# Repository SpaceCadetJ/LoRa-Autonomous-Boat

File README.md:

# LoRa Autonomous Boat Controller

An embedded-systems project spanning **STM32 firmware, LoRa communication, PCB reconstruction and a documented V2 redesign**. The original university boat controller is preserved as V1; the next vehicle node and a voice/text/location handheld are under development.

**Current milestone: engineering review edition.** The schematics, source code, parts and build procedures are available for inspection. V2 is not fabrication-ready, and the preserved V1 firmware build is not hardware-qualified.

[Portfolio case study](docs/portfolio/README.md) · [Application handbook](docs/applications/README.md) · [Build and assembly guide](docs/build/README.md) · [Latest verification](reviews/codex/design_completion/HANDOFF.md) · [Project history](REPORT.md)

| Existing controller | Developing controller |
| --- | --- |
|  |  |
| V1: 44 physical components, reconstructed from original fabrication evidence | V2: 118 physical references, 80 × 46 mm board draft |

These are CAD renders. They do not establish that the V2 board has been manufactured or tested.

## Explore the project

Clone or download the repository, then open [pm/index.html](pm/index.html) locally. For the complete interactive workspace with searchable BOMs, datasheets, drawings, connector evidence and assembly/programming guides:

```sh
node pm/tools/serve.mjs
```

Open **http://127.0.0.1:8765/pm/**. The viewer runs locally and requires no account or package installation. GitHub displays the HTML source; it does not run the viewer from a repository file link. See [viewer instructions](pm/README.md).

The [portfolio handoff](docs/portfolio/README.md) and [structured project data](docs/portfolio/portfolio.json) provide captions, asset paths, result evidence and claim boundaries for a portfolio site.

## Architecture and implementation

```mermaid
flowchart LR
  Handset[External handset] <-->|LoRa radio link| Radio[Reyax UART radio]
  Radio <-->|UART| MCU[STM32F446 vehicle controller]
  GPS[GNSS receiver] -->|NMEA UART| MCU
  MCU -->|PWM| ESC[Propulsion ESC]
  MCU -->|PWM| Servo[Steering servo]
  Battery[Battery and regulation] --> MCU
```

V1 firmware is bare-metal C using STM32 HAL/CMSIS, with UART radio commands, GPS parsing and two PWM outputs. The original handset source is not included. The current code has known failsafe, parsing and pin-role issues documented in the [firmware audit](docs/research/FIRMWARE_REVIEW_NOTES.md).

Hardware originated in Cadence OrCAD/Allegro and has been reconstructed in KiCad 9. Python tools generate and inspect schematics, compare complete pin groups and prepare assembly evidence. The viewer uses HTML, CSS and JavaScript with embedded project data; Node.js builds and validates it. GitHub Actions separates portable repository checks from optional native CAD and firmware jobs.

V2 adds draft provisions for protected power, a separate actuator rail, sensing and USB/debug access. The separate [Stage A diagnostic](firmware_v2/README.md) now builds for board identity and inactive actuator outputs. Corrected control firmware, autonomous navigation and the proposed voice/text/location handheld remain development targets. Voice airtime and RC coexistence must be validated before choosing handheld hardware.

## What has been demonstrated

| Deliverable | Recorded result | Evidence |
| --- | --- | --- |
| Readable schematic set | 15 annotated pages, visually inspected | [V1 PDF](docs/img/v1_schematic.pdf), [V2 PDF](docs/img/v2_schematic.pdf), [visual review](reviews/codex/professionalization/VISUAL_REVIEW.md) |
| Electrical preservation | All 172 V1 and 361 V2 pins preserved through the presentation changes | [Independent quality evidence](reviews/codex/professionalization/QUALITY_HANDOFF.md) |
| V1 firmware reconstruction | Two same-host builds produced identical ELF/HEX/BIN hashes; 36,528-byte BIN | [Build record](docs/build/FIRMWARE_HANDOFF.md) |
| Ordering and assembly | BOM reconciliation, held-part decisions, one-board/five-board candidate lists and assembly maps | [Ordering guide](docs/build/ORDERING.md) |
| Navigation and documentation | Searchable parts, selected datasheets, V1 connector atlas, source evidence and version-specific programming guides | [Workspace](pm/README.md), [build guide](docs/build/README.md) |
| Reproducible review | Regression tests, source hashes, native reports and preserved before/after evidence | [Review workflow](docs/build/REVIEW_WORKFLOW.md) |

The integrated V2 ground repair reduces **three unconnected PCB items to zero**, with zero ordinary DRC errors and unchanged warning/parity counts. The [fresh native review](reviews/codex/design_completion/native-review/REVIEW.md) preserves all 533 electrical pins. One V2 ERC warning remains; the strict review also flags the intentional PCB change against its older preservation baseline. Six [component-limit blockers](reviews/codex/design_completion/electrical/README.md) require circuit corrections before fabrication. No range, voice or autonomous-navigation performance is claimed by these software/CAD results.

## Build, review and contribute

- [V1 assembly and inspection](docs/build/ASSEMBLY_V1.md) · [V1 backup/flashing procedure](docs/build/FLASHING_V1.md)
- [V2 assembly review](docs/build/ASSEMBLY_V2.md) · [V2 firmware bring-up plan](docs/build/FLASHING_V2.md)
- [Safe schematic-only regeneration](docs/build/SCHEMATICS.md) · [Reproducible firmware build](docs/build/FIRMWARE_BUILD.md)
- [Independent review workflow](docs/build/REVIEW_WORKFLOW.md) · [Publication and portability record](reviews/codex/publication/README.md)

Do not run full PCB generation or routing merely to refresh drawings. The schematic-only command preserves the existing PCB, project and BOM. Native KiCad checks require KiCad 9; the V1 build requires the recorded GNU Arm toolchain. No CI job flashes real hardware.

The [IMU interface candidate](reviews/codex/imu_interface/README.md) now implements the proposed 1.8 V supply and I2C/interrupt translation in a separately checked schematic. It is available in the V2 viewer; live PCB integration is the next layout task.

## Next milestones

1. Correct the IMU's 1.8 V interface and the five remaining power/signal-limit findings; reconcile schematic-to-PCB differences.
2. Build on the separate Stage A diagnostic: freeze the operational protocol, implement supervised outputs and measure failsafe behavior.
3. Complete part/footprint qualification, the V2 connector atlas and staged physical bring-up.
4. Validate voice quality, radio airtime and RC scheduling before developing the handheld.

## Provenance and attribution

The original controller was a University of Arkansas EECS senior-design team project; the repository identifies May 2025 fabrication evidence. The current reconstruction, documentation and review tooling include AI-agent-assisted development. Individual original team contributions should be confirmed before using first-person portfolio claims.

`Allegro/` preserves original source evidence. Read [provenance and conversion limits](docs/A0_PROVENANCE.md) before interpreting the reconstructed geometry or inferred drill data. Third-party firmware and tools retain their existing notices; no new project-wide license is granted by this documentation.

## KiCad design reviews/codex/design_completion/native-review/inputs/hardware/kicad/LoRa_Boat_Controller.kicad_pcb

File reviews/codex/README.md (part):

# Start here: Codex review checkpoint

## Current actuator packet - ACT-04, 2026-10-12

The [isolated arm latch and annotated native sheets](actuator_latch/README.md) separate PC4 from OE while retaining R40 at OE. Native ERC is zero errors / the original AD0 warning; 396 existing memberships are preserved and exactly two change. The qualification and ACK sources remain unimplemented and default low. ACK while armed disables, a documented difference from ACT-03. Next: qualification/reset-release circuitry with fault retention and conditioned ACK; receiver readiness and watchdog sources remain held. This supersedes older next-task text below.

## Current actuator packet - ACT-03, 2026-10-12

The [interlock behavior and observability prototype](actuator_interlock/README.md) adds interactive fault scenarios, an executable deliberate-rearm contract and a receiver acceptance worksheet. Exact ACT-02 pin evidence confirms no receiver sensing and unused converter PG pins. No CAD/firmware change or new native acceptance is claimed. Next: isolated fault-dominant latch/OE gate with the PC4 request separated from OE and R40 retained; unimplemented qualifications must remain default-disabled. This supersedes older next-task text below.

## Current actuator packet - ACT-02, 2026-10-12

The [default-disabled translator and sequencing contract](actuator_enable/README.md) now has an annotated native schematic: TXU0102DCUR, PC4 arm signal and 10k hardware pulldown. Independent checks preserve 383 outside-boundary pins, both converters and ACT-01 source populations; 41 tests pass and ERC adds no findings. Firmware, ordering and live PCB are unchanged. Next: receiver-power observation and a hardware arm interlock, including independent ESC readiness in both populations. This supersedes older next-task text below.

## Current actuator packet - ACT-01, 2026-10-12

The [buffer supply and population review](actuator_supply/README.md) moves exactly four buffer/bypass pins to the dedicated 5 V converter, preserves both converter sheets and adds exact SMC diode identities with mutually exclusive BEC_ONLY/ONBOARD proposals. All 380 outside-boundary pins are preserved; no new ERC findings. A new C11 identity hold changes V2 ordering to 68 candidate / 39 held / 11 feature references, 35 candidate lines. Next: default-disabled buffer enable and power sequencing, followed by reservoir/transient and remaining integration gates. This supersedes older next-task text below.

## Current converter packet — BUCK5-A1, 2026-10-12

The [5 V converter and shared-feed review](buck_5v/README.md) now includes an annotated native LM76003 sheet: 119 components, 398 physical pins, all 339 outside-boundary pins preserved, zero ERC errors and the original warning. The first 3.3 V sheet is byte-identical. New SS34 SMC/SMA package findings are added to existing ordering holds; the 7 V full-load feed remains unqualified. Next: isolate the buffer supply from VSERVO and resolve exact OR-ing parts and supply population variants, then input-feed/leakage/damping and remaining integration gates. This entry supersedes older next-task text below.

## Current converter packet — BUCK33-A1, 2026-10-12

The [complete first 3.3 V converter](buck_3v3/README.md) now has a separate annotated sheet, exact supporting parts and native validation: 113 components, 361 pins, all 330 outside-boundary pins preserved, zero errors and the original ERC warning. This is an isolated INPUT-A1-derived candidate; live CAD, copper, purchasing and firmware remain unchanged. Capacitance, thermal, loop, input leakage and ADC gates remain open. Next: the isolated 5 V converter and its simultaneous-load budget, retaining 6S and the optional on-board actuator configuration. This entry supersedes older next-task text below.

## Current input-network packet — 2026-10-12

The [nonpolar reservoir and local bypass specification](input_capacitors/README.md) now includes exact screened identities, an annotated connection drawing, capacitance requirements and a native-checked TDK land-pattern proposal. No circuit changed; source damping, effective capacitance and complete leakage remain integration gates. Next: the isolated first 3.3 V wider-voltage converter cell with explicit pin delta and those holds retained. This entry supersedes older next-task text below.

## Latest circuit revision: IMU2

Start with [IMU2 and the next task](imu_bias_filter/README.md). The recommended 100 pF bias filter is verified in an isolated schematic; prior IMU1 and placement evidence remain immutable. Next: the 6S protection/power-package envelope, then complete-circuit routing.

## Latest bounded packet: placement feasibility

[Placement study and next task](imu_placement/README.md) preserves all original copper and placements. It verifies courtyard fit but rejects integration on untouched copper, with 136 native errors. Next: disposition the recommended bias filter and establish the 6S power-package envelope before final routing.

## Latest bounded packet: IMU interface candidate

[IMU candidate and next task](imu_interface/README.md) implements and independently checks the 1.8 V supply/bus/interrupt circuit in an isolated schematic. Live CAD and purchasing exports remain unchanged. Assess placement on a corrected PCB copy before integration.

## Current application and electrical completion packet

Start with [design_completion/HANDOFF.md](design_completion/HANDOFF.md), [application guides](../../docs/applications/README.md) and the [V2 diagnostic](../../firmware_v2/README.md). The current work connects application procedures to actual board/firmware readiness, repairs the three ground connections, identifies six component-limit blockers, and adds a pin-checked Stage A image. The previously published integration is on `main` and `v2-design`; earlier primary-ownership and no-push statements below are historical. Operational control firmware, electrical corrections and bench qualification remain separate open work.

## Earlier checkpoint — 2026-09-17, schematic and build review edition

Read [professionalization/HANDOFF.md](professionalization/HANDOFF.md) and [docs/build/README.md](../../docs/build/README.md) first. Jay authorized Codex to continue the professional schematics, purchasing/assembly, V1/V2 programming and review workflow while the other agent is inactive. Current ownership supersedes the earlier reservations below.

The delivered packet includes fifteen annotated schematic pages, verified preservation of 172 V1 / 361 V2 pins, a protected schematic-only generator command, ordering candidates/holds and assembly maps, a reproducible unqualified V1 firmware build, separate flashing guides and a manual CI definition. Strict combined review remains failed for one pre-existing V2 ERC warning. V2 also has three unconnected PCB entries, warnings/parity discrepancies and no firmware image; it is not fabrication-ready. The viewer now presents these current results beside the historic S2 evidence.

The next smallest packet is a pad-level disposition of the three V2 open connections and U6 AD0 warning, followed by a reviewed V2 pin/protocol contract. Avoid full CAD regeneration/rerouting during documentation work. All source/output hashes, reproduction commands and remaining limits are in the linked handoff. The hourly continuation prompt has been updated to this scope and remains quiet for non-actionable results.

## Previous checkpoint — 2026-09-17, viewer delivery

This section supersedes the initial intake state below. Resume through [pm/README.md](../../pm/README.md), then the latest root [handoff](../../HANDOFF.md) and [ownership](../../FILE_OWNERSHIP.md). Check Git status/HEAD before writing; the primary remains responsible for CAD, firmware, generators and Git integration. Codex owns `pm/**`, `docs/atlas/**`, `reviews/**`; coordination files are append-only.

- The local [interactive viewer](../../pm/index.html) includes V1 and V2 design assets, searchable BOMs and selected manufacturer references, the V1 connector atlas, source/protocol proposals, independent versus reported checks, findings-to-requirements links, decisions, documents and exported review notes. It opens directly or through the loopback server described in its README.
- [V1 atlas](../../docs/atlas/README.md): 12 connectors/test points and 36 pins, traced from source evidence with firmware citations. Physical orientation and bench readings remain unverified. V2 atlas is not yet done.
- [S2 independent verification](S2_VERIFICATION.md): historic `639e08f` only. All 172 pins / 44 parts agree, ERC 0, DRC 0 errors / 0 unconnected / 67 warnings, hole centers 53/53. Additional native parity: 139 classified metadata warnings. No electrical mismatch found; no-change schematic update workflow and V5 drill sizes remain unverified. The earlier global blocked label was narrowed; raw results did not change.
- Primary V2 release at `a6316e9` / `v2-design-draft` reports 118 parts, 71 nets, 68 grouped BOM lines and two open ground connections. The current CSV independently parses as 67 component rows totaling 118 parts; the report count is stale. Treat V2 numbers as reported, pending independent verification. Current source documents contain 35 distinct V1 findings and 45 requirements.
- Standalone files in `firmware_prototype/` are uncompiled review proposals. No functional firmware fix was integrated.
- Jay requires **voice + text + location**. The primary handoff additionally reports expanded vehicle/fleet scope; wait for its architecture/requirements documents before asserting that expanded scope is implemented. Validate voice/RC coexistence before radio selection. `REQ-CTL-01` currently says a default **1.0 s** loss timeout; the primary prompt's **500 ms** summary conflicts and must be reconciled in the RF packet.

**Next smallest packet:** independently snapshot the released V2 inputs, record hashes and run ERC/DRC plus part/net/BOM inventory in `reviews/codex/` without invoking generators or changing source CAD. Then review one power/control subsystem against actual requirements. Later packets: V2 atlas, protocol prototype build/tests, quantitative voice/RC coexistence, handheld/application views from released documents.

An hourly continuation automation is active. It works bounded packets in released scopes and should notify only on meaningful deliverables, new blocking findings or required decisions. Account/runtime availability may interrupt runs; these files are the durable resume context.

## Historical initial intake — retained for context

Updated 2026-09-17 UTC. User objective: understand and improve the conversion, documentation and readability first; develop a general-purpose LoRa controller family later. Primary agent is still active. Codex has made no CAD, firmware, source-evidence or Git-history changes.

## Read in this order

1. This file and root [ownership](../../FILE_OWNERSHIP.md), [handoff](../../HANDOFF.md), [status](../../AGENT_STATUS.md).
2. [Assessment](ASSESSMENT.md): corrected baseline, findings, gate matrix and safe continuation.
3. [Platform concept](PLATFORM_CONCEPT.md): block/state diagrams, shared interfaces and documentation design.
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
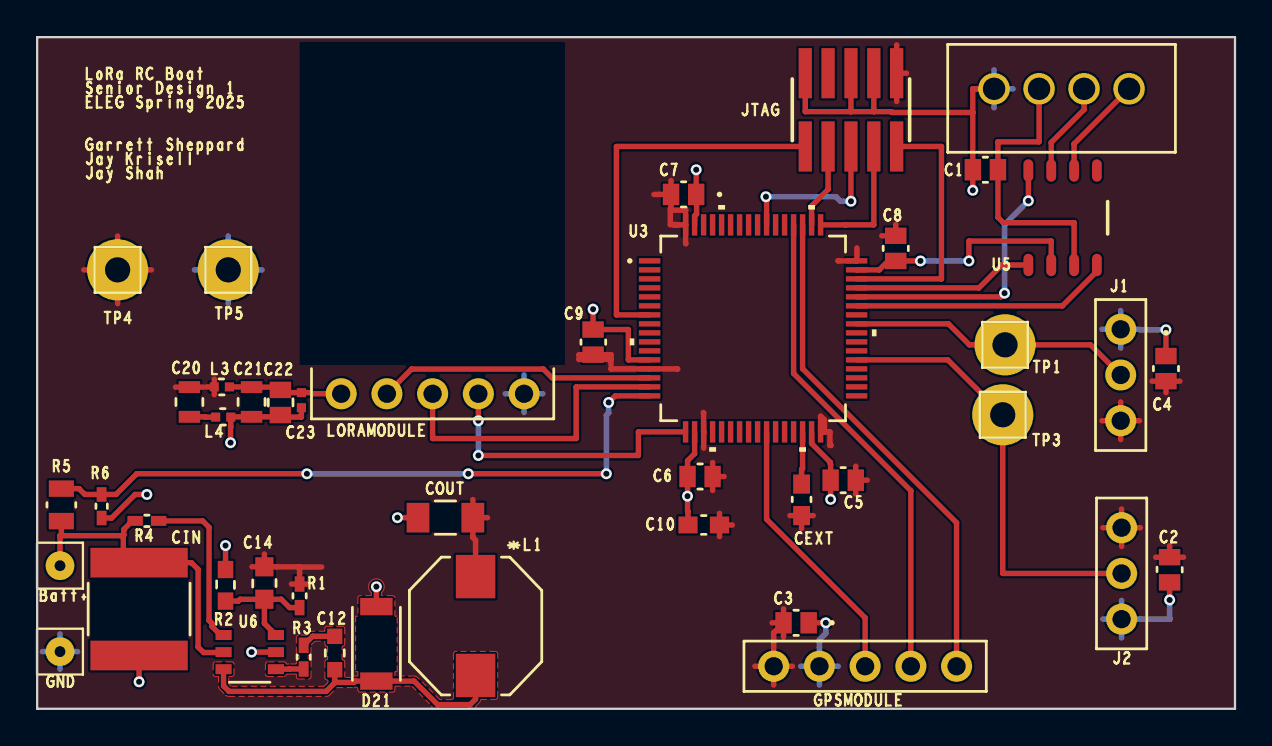
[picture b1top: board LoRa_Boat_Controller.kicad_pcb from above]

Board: 2 copper layers, 66.5 x 37.3 mm, 44 parts (0 on the bottom side), 31 nets.

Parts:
C1, C2, C3, C4, C5, C6, C7, C8, C9, C22: .1uF; CAP_KGM21_KAV-L
C10: 4.7uF; CAP_0603_CL10A_1P6XP8_SAM-M
C12: .1uf; CAP_CL10_SAM-M
C14: 470pF; CAP_0603G_AVX-M
C20, C21: 10uF; G-21_MUR-L
C23: 47pF; CAP_GJM1555C1H220JB01__MUR-L
CANHEADER1: CONN_B4B-XH-A; CONN_B4B-XH-A_JST
CEXT1: 4.7 uF; CAP_0603_CL10A_1P6XP8_SAM-M
CIN1: 10uF; CAP_NTS_55_2P8T_NIP
COUT1: 10uf; G-31_MUR-M
D21: DIODE_MFLAT; M-FLAT_TOS-L
GND1: Battery-; amv_con1
GPSMODULE1: CONN5_1LFBN-RC; CONN5_1LFBN-RC_SUL
JTAG1: FTSH-105-XX-X-DV; SAMTEC_FTSH-105-XX-X-DV
L1: 4.7uh; IND_7045_TDK
L3, L4: INDUCTOR; IND_BLM15_0402_MUR-L
LORAMODULE1: CONN5_1LFBN-RC; CONN5_1LFBN-RC_SUL
R1: 15K; RC0402N_PAN-M
R2: 4.7K; RC0603N_YAG-M
R3: 51; RC0402N_YAG-M
R4: 5.1K; RC0402N_PAN-M
R5: 30K; RES_R0805_ROM-M
R6: 10K; RES_1005_SAM-M
SPEEDCONTROLLER1: CONN_PPTC031; CONN_PPTC031_SUL
STEERINGSERVO1: CONN_PPTC031; CONN_PPTC031_SUL
TP1, TP3, TP4, TP5: TEST POINT; amv_test_point
U3: STM32F4XXR2; LQFP64-10x10mm
U5: TCAN1042H-Q1D; D0008A_L
U6: R1240N001x; SOT-23-6W_PE-SOT23-6W-0512_NMD
VIN1: Battery+; amv_con1

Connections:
+3V3: C2.2, C3.2, C4.2, C5.2, C6.2, C7.2, C8.2, C9.2, C10.2, C14.1, C20.2, CEXT1.2, COUT1.2, GPSMODULE1.1, JTAG1.1, L1.1, L3.2, R1.1, SPEEDCONTROLLER1.1, STEERINGSERVO1.1, TP4.1, U3.13 (VDDA/VREF+), U3.19 (VDD), U3.32 (VDD_2), U3.48 (VDD_3), U3.64 (VDD_4)
ADC_VBAT: R5.2, R6.2, U3.16 (PA2)
BST: R3.2, U6.4 (BST)
BST_RC: C12.2, R3.1
CANH: CANHEADER1.3, U5.7 (CANH)
CANL: CANHEADER1.4, U5.6 (CANL)
CAN_RXD_PA10: U3.43 (PA10), U5.4 (RXD)
CAN_STB_PA11: U3.44 (PA11), U5.8 (STB)
CAN_TXD_PA12: U3.45 (PA12), U5.1 (TXD)
CAN_VCC: C1.2, CANHEADER1.2, U5.3 (VCC)
EN: R4.2, U6.1 (CE)
FB_DIV: C14.2, R1.2, R2.1, U6.6 (VFB)
GND: C1.1, C2.1, C3.1, C4.1, C5.1, C6.1, C7.1, C8.1, C9.1, C10.1, C21.1, C22.1, C23.1, CANHEADER1.1, CIN1.1, COUT1.1, D21.1, GND1.1, GPSMODULE1.2, JTAG1.3, JTAG1.5, JTAG1.9, L4.1, LORAMODULE1.5, R2.2, R6.1, SPEEDCONTROLLER1.3, STEERINGSERVO1.3, TP5.1, U3.12 (VSSA/VREF-), U3.18 (VSS), U3.31 (VSS_2), U3.47 (VSS_3), U3.63 (VSS_4), U5.2 (GND), U6.5 (GND)
GPS_PB0: GPSMODULE1.3, U3.26 (PB0)
GPS_RX_PC11: GPSMODULE1.4, U3.52 (PC11)
GPS_TX_PC10: GPSMODULE1.5, U3.51 (PC10)
LORA_FILT: C20.1, L4.2
LORA_RST_PA3: LORAMODULE1.4, U3.17 (PA3)
LORA_RX_PA1: LORAMODULE1.3, U3.15 (PA1)
LORA_TX_PA0: LORAMODULE1.2, U3.14 (PA0)
LORA_VCC: C21.2, C22.2, C23.2, L3.1, LORAMODULE1.1
NRST: JTAG1.10, U3.7 (NRST)
PWM_PA8_ESCHDR: SPEEDCONTROLLER1.2, TP1.1, U3.41 (PA8)
PWM_PC6_SERVOHDR: STEERINGSERVO1.2, TP3.1, U3.37 (PC6)
SWCLK: JTAG1.4, U3.49 (PA14)
SWDIO: JTAG1.2, U3.46 (PA13)
SWO_TDO: JTAG1.6, U3.55 (PB3)
SW_NODE: C12.1, D21.2, L1.2, U6.3 (LX)
TDI: JTAG1.8, U3.50 (PA15)
VCAP1: CEXT1.1, U3.30 (VCAP_1)
VIN_RAW: CIN1.2, R4.1, R5.1, U6.2 (VIN), VIN1.1

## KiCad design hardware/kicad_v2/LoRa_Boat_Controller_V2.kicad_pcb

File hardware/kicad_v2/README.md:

# LoRa Boat Controller V2 — KiCad 9 project (Phase C draft)

Electrical intent is generated from `tools/v2_design.py`; schematic presentation is controlled by `../kicad/tools/schematic_layout.py` and the shared renderer. Keep source and generated outputs together. The [build guide](../../docs/build/README.md), [schematic editing procedure](../../docs/build/SCHEMATICS.md) and [current independent checks](../../reviews/codex/professionalization/QUALITY_HANDOFF.md) describe the latest review packet. Existing PCB routing is preserved by schematic-only commands.

| File | What it is |
|---|---|
| `LoRa_Boat_Controller_V2.kicad_pro` | project: netclasses (Default 0.25 mm / 0.15 mm, Power 0.6 mm / 0.2 mm), DRC severities, board rules (0.127 mm min clearance / track, 0.3 mm edge, 0.6 mm min via) |
| `LoRa_Boat_Controller_V2.kicad_sch` + `Power/MCU/Radio/Navigation/Actuators/Debug.kicad_sch` | root sheet with hierarchical pins + six sub-sheets (ERC: 0 errors, 1 accepted warning — U6 SDO/AD0 tied to GND) |
| `LoRa_Boat_Controller_V2.kicad_pcb` | 80 × 46 mm 2-layer board, 118 footprints, GND pours both sides, autorouted with freerouting (see `tools/route_v2.py`) |
| `LoRa_Boat_Controller_V2.kicad_sym` / `.pretty/` | project symbols (VSERVO) and footprints (QFN-24 3 × 3 mm 0.4 mm no-EP for the ICM-20948) |
| `fp-lib-table`, `sym-lib-table` | project libraries: `LoRa_Boat_Controller` (reused V1 footprints/symbols from `../kicad/`) and `LoRa_Boat_Controller_V2` |
| `_build/` | (git-ignored) DSN/SES, freerouting log, DRC/ERC reports, placement report, BOM JSON |

## Tool chain (run from the repo root)

```bash
python hardware/kicad_v2/tools/gen_v2.py check                                   # design-rule sanity: every pin either in a net or in NC_PINS
python hardware/kicad_v2/tools/gen_v2.py sch                                     # schematic-only refresh; preserves PCB/project/BOM
python hardware/kicad/tools/export_review.py                                    # PDF/SVG rendering only; no CAD generation
"C:/Users/Jay/AppData/Local/Programs/KiCad/9.0/bin/python.exe" hardware/kicad_v2/tools/placement_check.py   # courtyard overlaps / parts off the board
"C:/Users/Jay/AppData/Local/Programs/KiCad/9.0/bin/kicad-cli.exe" sch erc --severity-all -o hardware/kicad_v2/_build/erc.rpt hardware/kicad_v2/LoRa_Boat_Controller_V2.kicad_sch
"C:/Users/Jay/AppData/Local/Programs/KiCad/9.0/bin/python.exe" hardware/kicad_v2/tools/route_v2.py all     # DSN (B.Cu GND plane only) -> freerouting -> SES import -> pour fill
"C:/Users/Jay/AppData/Local/Programs/KiCad/9.0/bin/kicad-cli.exe" pcb drc --severity-error -o hardware/kicad_v2/_build/drc.rpt hardware/kicad_v2/LoRa_Boat_Controller_V2.kicad_pcb
```

`gen_v2.py pcb` explicitly replaces the PCB with an unrouted board; `gen_v2.py all` (also the legacy no-argument default) regenerates libraries, schematic, project, unrouted PCB and BOM. Use those only for an intentional full rebuild. `check`, `bom` and `sch` have separate scopes; `sch` no longer destroys routing. An isolated regression test verifies that separation.

`route_v2.py` needs Java 21 and `freerouting-2.1.0.jar` at `%LOCALAPPDATA%\freerouting\` (or `FREEROUTING_JAR`). Routing is separate from schematic presentation; do not reroute merely to refresh drawings. The routing command above remains an explicit board mutation, outside the presentation-only workflow.

## Design source (`tools/v2_design.py`)

- `PARTS`: ref -> (symbol, footprint, value, MPN, manufacturer, sheet, description). `NETS`: net -> pins as `REF-number` or `REF.pinname`. `NC_PINS`: pins deliberately left open (everything else must be in a net, `gen_v2.py check` fails otherwise).
- `POWER_NETS`: which nets are drawn with power symbols; `SHEETS`: sheet names/paper/descriptions; `PLACE`: ref -> (x, y, rotation) in board mm from the top-left corner; `MOUNT_HOLES`, `BOARD_W/H`, `KEEPOUTS`.
- `PRICE_USD` / `PRICE_DATE`: qty-1 catalogue prices used by `docs/BOM_V2.csv` (estimates; re-quote at order time).

Requirement traceability is in the schematic sheet descriptions and in `docs/V2_REQUIREMENTS.md` (REQ-xx ids); the design decisions still open for Jay are in `BLOCKERS.md`.

## Known state of this draft

Current independent results supersede the historical routing count below: **3 unconnected entries, 101 DRC warnings, 212 schematic-parity entries**, zero DRC errors; ERC has one pre-existing U6 AD0 pin-type warning. No fabrication acceptance. [Assembly maps and procedures](../../docs/build/ASSEMBLY_V2.md) are now available; physical orientation and device/footprint qualification remain open.

- DRC 0 violations, **2 unconnected GND connections**: two pour islands (near U1 at board (42, 18.5) mm and near U7 at (55.7, 9.2) mm) are fenced in by other-net tracks on both layers. `route_v2.py import` stitches what it can (one of three islands on this layout); the last two need a hand-placed via each in KiCad (or a rip-up of the fencing track). The next layout pre-places a GND via next to every fine-pitch GND pad before routing to avoid this.
- Autorouted, not hand-optimised: expect to tidy the buck-converter loops (U2/L1/D3/C5-C6 and U3/L2/D4/C8-C9), the crystal traces and the USB pair before fabrication; keep the placement.
- Silkscreen is reference designators only; no assembly drawing yet.
- Footprints for new parts come from the KiCad 9 standard library on this machine (`KICAD_FOOTPRINT_DIR`), embedded into the board at generation time.

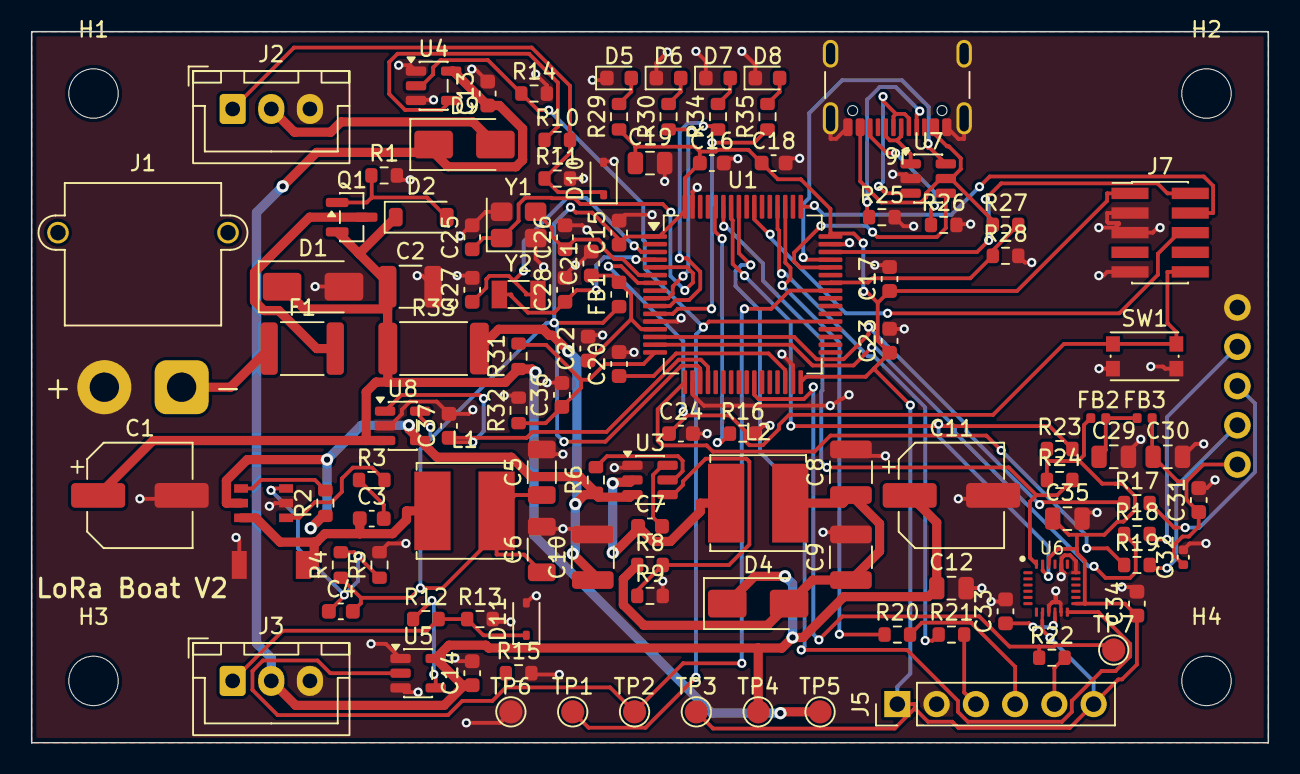
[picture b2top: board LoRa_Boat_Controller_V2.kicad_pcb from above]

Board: 2 copper layers, 80.0 x 46.0 mm, 118 parts (0 on the bottom side), 71 nets.

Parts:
C1: 47uF 50V; CP_Elec_6.3x7.7
C2, C10: 10uF 50V; C_1210_3225Metric
C3: 100nF 50V; C_0603_1608Metric
C4: 470pF; C_0603_1608Metric
C5, C6: 10uF 25V; C_1206_3216Metric
C7, C13, C14, C15, C16, C17, C18, C22, C23, C24, C31, C33, C34, C36, C37: 100nF; C_0603_1608Metric
C8, C9: 22uF 16V; C_1210_3225Metric
C11: 100uF 10V; CP_Elec_6.3x7.7
C12: 10uF 16V; C_0805_2012Metric
C19, C29, C30, C35: 10uF 10V; C_0805_2012Metric
C20: 4.7uF 10V; C_0603_1608Metric
C21: 1uF; C_0603_1608Metric
C25, C26: 15pF C0G; C_0603_1608Metric
C27, C28: 10pF C0G; C_0603_1608Metric
C32: 47pF; C_0402_1005Metric
D1: SMAJ33A; D_SMA
D2: 10V; D_SOD-123
D3: CMS06; M-FLAT_TOS-L
D4, D9: SS34; D_SMA
D5: PWR green; LED_0603_1608Metric
D6: LINK blue; LED_0603_1608Metric
D7: FIX yellow; LED_0603_1608Metric
D8: FAULT red; LED_0603_1608Metric
D10, D11: PESD5V0S1BA; D_SOD-323
F1: 3A; Fuse_1812_4532Metric
FB1: 600R; L_0603_1608Metric
FB2, FB3: 600R; L_0402_1005Metric
H1, H2, H3, H4: M3; MountingHole_3.2mm_M3
J1: BATTERY XT30; AMASS_XT30PW-M_1x02_P2.50mm_Horizontal
J2: ESC; JST_XH_B3B-XH-A_1x03_P2.50mm_Vertical
J3: SERVO; JST_XH_B3B-XH-A_1x03_P2.50mm_Vertical
J4: LoRa RYLR998; CONN5_1LFBN-RC_SUL
J5: GNSS; PinHeader_1x06_P2.54mm_Vertical
J6: USB-C; USB_C_Receptacle_GCT_USB4105-xx-A_16P_TopMnt_Horizontal
J7: SWD; PinHeader_2x05_P1.27mm_Vertical_SMD
L1, L2: 4.7uH 3A; L_Bourns_SRN6045TA
Q1: AO3401A; SOT-23
R1, R6, R8, R14, R15: 100k; R_0603_1608Metric
R2, R25, R26: 5.1k; R_0603_1608Metric
R3: 51R; R_0603_1608Metric
R4: 15k; R_0603_1608Metric
R5: 4.7k; R_0603_1608Metric
R9: 13.3k; R_0603_1608Metric
R10, R12, R17, R18, R19, R20, R21, R22: 100R; R_0603_1608Metric
R11, R13, R16: 10k; R_0603_1608Metric
R23, R24: 2.2k; R_0603_1608Metric
R27, R28, R31: 47k; R_0603_1608Metric
R29, R30, R34, R35: 1k; R_0603_1608Metric
R32: 6.8k; R_0603_1608Metric
R33: 0.02R 1W; R_2512_6332Metric
SW1: RESET; SW_Push_1P1T_NO_CK_KMR2
TP1: ESC_PWM; TestPoint_Pad_D1.5mm
TP2: SERVO_PWM; TestPoint_Pad_D1.5mm
TP3: +3V3; TestPoint_Pad_D1.5mm
TP4: VSERVO; TestPoint_Pad_D1.5mm
TP5: VIN_RAW; TestPoint_Pad_D1.5mm
TP6: GND; TestPoint_Pad_D1.5mm
TP7: PPS; TestPoint_Pad_D1.5mm
U1: STM32F446RET6; LQFP-64_10x10mm_P0.5mm
U2: R1240N001B-TR-FE; SOT-23-6W_PE-SOT23-6W-0512_NMD
U3: TPS54202; TSOT-23-6
U4, U5: 74AHCT1G125; SOT-23-5
U6: ICM-20948; QFN-24_3x3mm_P0.4mm_NoEP
U7: USBLC6-2SC6; SOT-23-6
U8: INA180A1; SOT-23-5
Y1: 8MHz; Crystal_SMD_3225-4Pin_3.2x2.5mm
Y2: 32.768kHz; Crystal_SMD_3215-2Pin_3.2x1.5mm

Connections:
+3V3: C4.2, C5.1, C6.1, C15.1, C16.1, C17.1, C18.1, C19.1, C23.1, C34.1, C35.1, FB1.1, FB2.1, J5.1, J5.6, J7.1, L1.2, R4.1, R23.1, R24.1, R29.1, TP3.1, U1.1, U1.19, U1.32, U1.48, U1.64, U6.8, U6.13, U6.22, U8.5
+5V_BUCK: C8.1, C9.1, D4.2, L2.2, R8.1
BEC_IN: D9.2, J2.2
BOOT0: R16.1, U1.60
BOOT_5V: C7.2, U3.6
BST_3V3: R3.2, U2.4
BST_RC: C3.2, R3.1
EN_3V3: R2.2, U2.1
EN_5V: R6.2, U3.5
ESC_SIG: D10.1, J2.1, R10.2, R11.1
ESC_SIG_5V: R10.1, U4.4
FB_3V3: C4.1, R4.2, R5.1, U2.6
FB_5V: R8.2, R9.1, U3.4
GND: C1.2, C2.2, C5.2, C6.2, C8.2, C9.2, C10.2, C11.2, C12.2, C13.2, C14.2, C15.2, C16.2, C17.2, C18.2, C19.2, C20.2, C21.2, C22.2, C23.2, C24.2, C25.2, C26.2, C27.2, C28.2, C29.2, C30.2, C31.2, C32.2, C33.2, C34.2, C35.2, C36.2, C37.2, D1.2, D3.1, D5.1, D6.1, D7.1, D8.1, D10.2, D11.2, J1.2, J2.3, J3.3, J4.5, J5.2, J6.A1, J6.A12, J6.B1, J6.B12, J6.S1, J7.3, J7.5, J7.9, R1.2, R5.2, R9.2, R11.2, R13.2, R14.2, R15.2, R16.2, R25.2, R26.2, R28.2, R32.2, SW1.2, TP6.1, U1.12, U1.18, U1.31, U1.47, U1.63, U2.5, U3.1, U4.1, U4.3, U5.1, U5.3, U6.9, U6.11, U6.18, U6.20, U7.2, U8.2, Y1.2, Y1.4
GNSS_PPS: J5.5, R22.2
GNSS_RXD: J5.4, R20.2
GNSS_RX_PC11: R21.1, U1.52
GNSS_TXD: J5.3, R21.2
GNSS_TX_PC10: R20.1, U1.51
HSE_IN: C25.1, U1.5, Y1.1
HSE_OUT: C26.1, U1.6, Y1.3
I2C1_SCL: R23.2, U1.58, U6.23
I2C1_SDA: R24.2, U1.59, U6.24
IMU_INT: U1.57, U6.12
IMU_REGOUT: C33.1, U6.10
ISENSE: C37.1, U1.20, U8.1
LED_FAULT: R35.1, U1.11
LED_FAULT_A: D8.2, R35.2
LED_FIX: R34.1, U1.10
LED_FIX_A: D7.2, R34.2
LED_LINK: R30.1, U1.9
LED_LINK_A: D6.2, R30.2
LED_PWR: D5.2, R29.2
LORA_FILT: C29.1, FB2.2, FB3.1
LORA_NRST: J4.2, R19.2
LORA_NRST_PA3: R19.1, U1.17
LORA_RXD: J4.3, R17.2
LORA_RX_PA1: R18.1, U1.15
LORA_TXD: J4.4, R18.2
LORA_TX_PA0: R17.1, U1.14
LORA_VCC: C30.1, C31.1, C32.1, FB3.2, J4.1
LSE_IN: C27.1, U1.3, Y2.1
LSE_OUT: C28.1, U1.4, Y2.2
NRST: C24.1, J7.10, SW1.1, U1.7
PGATE: D2.2, Q1.1, R1.1
PPS_PB0: R22.1, TP7.1, U1.26
PWM_ESC_PC6: R14.1, TP1.1, U1.37, U4.2
PWM_SERVO_PA8: R15.1, TP2.1, U1.41, U5.2
SERVO_SIG: D11.1, J3.1, R12.2, R13.1
SERVO_SIG_5V: R12.1, U5.4
SWCLK: J7.4, U1.49
SWDIO: J7.2, U1.46
SWO: J7.6, U1.55
SW_3V3: C3.1, D3.2, L1.1, U2.3
SW_5V: C7.1, L2.1, U3.2
USB_CC1: J6.A5, R25.1
USB_CC2: J6.B5, R26.1
USB_DM: U1.44, U7.4
USB_DM_CONN: J6.A7, J6.B7, U7.3
USB_DP: U1.45, U7.6
USB_DP_CONN: J6.A6, J6.B6, U7.1
VBAT_FUSED: F1.2, Q1.3
VBAT_IN: F1.1, J1.1
VBAT_SENSE: C36.1, R31.2, R32.1, U1.16
VBUS: J6.A4, J6.A9, J6.B4, J6.B9, R27.1, U7.5
VBUS_SENSE: R27.2, R28.1, U1.42
VCAP1: C20.1, U1.30
VDDA: C21.1, C22.1, FB1.2, U1.13
VIN_BUCK: C10.1, R2.1, R6.1, R33.2, U2.2, U3.3, U8.4
VIN_RAW: C1.1, C2.1, D1.1, D2.1, Q1.2, R31.1, R33.1, TP5.1, U8.3
VSERVO: C11.1, C12.1, C13.1, C14.1, D4.1, D9.1, J3.2, TP4.1, U4.5, U5.5

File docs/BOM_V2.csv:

Item,Qty,Refs,Value,MPN,Manufacturer,Description,Footprint,Sheet,Unit price qty1 USD,Ext price USD
1,1,J1,BATTERY XT30,XT30PW-M,Amass,"Battery input 7-25 V, board only (<= 3 A)",Connector_AMASS:AMASS_XT30PW-M_1x02_P2.50mm_Horizontal,Power,1.20,1.20
2,1,F1,3A,0468003.NR,Littelfuse,3 A fast-acting 1812 fuse on the board feed,Fuse:Fuse_1812_4532Metric,Power,0.55,0.55
3,1,Q1,AO3401A,AO3401A,Alpha & Omega,"P-MOSFET reverse-polarity protection (-30 V, 4 A)",Package_TO_SOT_SMD:SOT-23,Power,0.35,0.35
4,1,D2,10V,BZT52C10-7-F,Diodes Inc,"Gate-source clamp for Q1 (10 V: AO3401A Vgs max is 12 V, review A-10)",Diode_SMD:D_SOD-123,Power,0.15,0.15
5,5,R1 R6 R8 R14 R15,100k,RC0603FR-07100KL,Yageo,Q1 gate pull-down,Resistor_SMD:R_0603_1608Metric,Power,0.10,0.50
6,1,D1,SMAJ33A,SMAJ33A,Littelfuse,33 V unidirectional TVS on VIN_RAW (pin 1 = cathode to VIN_RAW),Diode_SMD:D_SMA,Power,0.45,0.45
7,1,C1,47uF 50V,EEE-FK1H470P,Panasonic,Bulk input capacitor,Capacitor_SMD:CP_Elec_6.3x7.7,Power,0.60,0.60
8,2,C2 C10,10uF 50V,GRM32ER71H106KA12L,Murata,Input ceramic,Capacitor_SMD:C_1210_3225Metric,Power,0.85,1.70
9,1,R33,0.02R 1W,CRA2512-FZ-R020ELF,Bourns,Board current shunt (REQ-PWR-06),Resistor_SMD:R_2512_6332Metric,Power,0.55,0.55
10,1,U8,INA180A1,INA180A1IDBVR,Texas Instruments,"Current-sense amplifier, gain 20 (3 A = 1.2 V)",Package_TO_SOT_SMD:SOT-23-5,Power,0.95,0.95
11,15,C37 C36 C7 C15 C16 C17 C18 C22 C23 C24 C31 C33 C34 C13 C14,100nF,KGM15ACG1H104KT,Kyocera AVX,INA180 output filter,Capacitor_SMD:C_0603_1608Metric,Power,0.10,1.50
12,3,R31 R27 R28,47k,RC0603FR-0747KL,Yageo,Battery divider top (26 V -> 3.3 V),Resistor_SMD:R_0603_1608Metric,Power,0.10,0.30
13,1,R32,6.8k,RC0603FR-076K8L,Yageo,Battery divider bottom,Resistor_SMD:R_0603_1608Metric,Power,0.10,0.10
14,1,U2,R1240N001B-TR-FE,R1240N001B-TR-FE,Nisshinbo,"1.25 MHz async buck, 1.2 A",LoRa_Boat_Controller:SOT-23-6W_PE-SOT23-6W-0512_NMD,Power,1.45,1.45
15,3,R2 R25 R26,5.1k,RC0603FR-075K1L,Yageo,CE pull-up to VIN_BUCK,Resistor_SMD:R_0603_1608Metric,Power,0.10,0.30
16,1,R3,51R,RC0603FR-0751RL,Yageo,Bootstrap series R (per DS),Resistor_SMD:R_0603_1608Metric,Power,0.10,0.10
17,1,C3,100nF 50V,CL10B104KB8NNNC,Samsung,Bootstrap capacitor,Capacitor_SMD:C_0603_1608Metric,Power,0.10,0.10
18,2,L1 L2,4.7uH 3A,SRN6045TA-4R7M,Bourns,Replaces the EOL SLF7045 (F-BOM-01),Inductor_SMD:L_Bourns_SRN6045TA,Power,0.55,1.10
19,1,D3,CMS06,"CMS06(TE12L,Q,M)",Toshiba,Catch diode 30 V 2 A,LoRa_Boat_Controller:M-FLAT_TOS-L,Power,0.60,0.60
20,1,R4,15k,RC0603FR-0715KL,Yageo,FB top: Vout = 0.8 * (1 + 15/4.7) = 3.35 V,Resistor_SMD:R_0603_1608Metric,Power,0.10,0.10
21,1,R5,4.7k,RC0603FR-074K7L,Yageo,FB bottom,Resistor_SMD:R_0603_1608Metric,Power,0.10,0.10
22,1,C4,470pF,06035A471JAT2A,Kyocera AVX,Feed-forward (CSPD),Capacitor_SMD:C_0603_1608Metric,Power,0.15,0.15
23,2,C5 C6,10uF 25V,GRM31CR71E106KA12L,Murata,3.3 V output,Capacitor_SMD:C_1206_3216Metric,Power,0.45,0.90
24,1,U3,TPS54202,TPS54202DDCR,Texas Instruments,5 V / 2 A buck for the servo rail (populate option),Package_TO_SOT_SMD:TSOT-23-6,Power,0.75,0.75
25,1,R9,13.3k,RC0603FR-0713K3L,Yageo,FB bottom,Resistor_SMD:R_0603_1608Metric,Power,0.10,0.10
26,2,C8 C9,22uF 16V,GRM32ER61C226KE20L,Murata,5 V output,Capacitor_SMD:C_1210_3225Metric,Power,0.60,1.20
27,2,D4 D9,SS34,SS34,Vishay,OR-ing: on-board 5 V -> VSERVO,Diode_SMD:D_SMA,Power,0.35,0.70
28,1,C11,100uF 10V,EEE-FK1A101P,Panasonic,VSERVO bulk,Capacitor_SMD:CP_Elec_6.3x7.7,Power,0.40,0.40
29,1,C12,10uF 16V,GRM21BR61C106KE15L,Murata,VSERVO ceramic,Capacitor_SMD:C_0805_2012Metric,Power,0.25,0.25
30,1,U1,STM32F446RET6,STM32F446RET6,STMicroelectronics,Cortex-M4 180 MHz,Package_QFP:LQFP-64_10x10mm_P0.5mm,MCU,9.80,9.80
31,4,C19 C29 C30 C35,10uF 10V,GRM21BR61A106KE19L,Murata,VDD bulk,Capacitor_SMD:C_0805_2012Metric,MCU,0.20,0.80
32,1,C20,4.7uF 10V,CL10A475KP8NNNC,Samsung,"VCAP_1 to VSS (REQ-MCU-01, fixes F-MCU-01)",Capacitor_SMD:C_0603_1608Metric,MCU,0.12,0.12
33,1,FB1,600R,BLM18AG601SN1D,Murata,VDDA filter,Inductor_SMD:L_0603_1608Metric,MCU,0.12,0.12
34,1,C21,1uF,CL10A105KB8NNNC,Samsung,VDDA,Capacitor_SMD:C_0603_1608Metric,MCU,0.10,0.10
35,3,R16 R11 R13,10k,RC0603FR-0710KL,Yageo,BOOT0 pull-down (REQ-MCU-02),Resistor_SMD:R_0603_1608Metric,MCU,0.10,0.30
36,1,SW1,RESET,KMR221GLFS,C&K,Reset button,Button_Switch_SMD:SW_Push_1P1T_NO_CK_KMR2,MCU,0.65,0.65
37,1,Y1,8MHz,ABM8-8.000MHZ-10-1-U-T,Abracon,"HSE, CL 10 pF (REQ-MCU-03)",Crystal:Crystal_SMD_3225-4Pin_3.2x2.5mm,MCU,0.95,0.95
38,2,C25 C26,15pF C0G,06035A150JAT2A,Kyocera AVX,HSE load,Capacitor_SMD:C_0603_1608Metric,MCU,0.15,0.30
39,1,Y2,32.768kHz,ABS07-32.768KHZ-7-T,Abracon,"LSE, CL 7 pF (REQ-MCU-04, populate option)",Crystal:Crystal_SMD_3215-2Pin_3.2x1.5mm,MCU,0.70,0.70
40,2,C27 C28,10pF C0G,06035A100JAT2A,Kyocera AVX,LSE load,Capacitor_SMD:C_0603_1608Metric,MCU,0.15,0.30
41,1,D5,PWR green,LTST-C193KGKT-5A,Lite-On,Power LED (REQ-PWR-08),LED_SMD:LED_0603_1608Metric,MCU,0.30,0.30
42,1,D6,LINK blue,LTST-C193TBKT-5A,Lite-On,Link LED,LED_SMD:LED_0603_1608Metric,MCU,0.30,0.30
43,1,D7,FIX yellow,LTST-C193KSKT-5A,Lite-On,GNSS fix LED,LED_SMD:LED_0603_1608Metric,MCU,0.30,0.30
44,1,D8,FAULT red,LTST-C193KRKT-5A,Lite-On,Fault / failsafe LED,LED_SMD:LED_0603_1608Metric,MCU,0.30,0.30
45,4,R29 R30 R34 R35,1k,RC0603FR-071KL,Yageo,LED,Resistor_SMD:R_0603_1608Metric,MCU,0.10,0.40
46,1,J4,LoRa RYLR998,PPTC051LFBN-RC,Sullins,"1x5 socket: VDD, NRST, RXD, TXD, GND (RYLR998 pinout)",LoRa_Boat_Controller:CONN5_1LFBN-RC_SUL,Radio,0.60,0.60
47,2,FB2 FB3,600R,BLM15AG601SN1D,Murata,LoRa supply pi filter,Inductor_SMD:L_0402_1005Metric,Radio,0.12,0.24
48,1,C32,47pF,GJM1555C1H470JB01D,Murata,LORA_VCC (RYLR998 reference design),Capacitor_SMD:C_0402_1005Metric,Radio,0.12,0.12
49,8,R17 R18 R19 R20 R21 R22 R10 R12,100R,RC0603FR-07100RL,Yageo,UART4_TX series,Resistor_SMD:R_0603_1608Metric,Radio,0.10,0.80
50,1,J5,GNSS,PPTC061LFBN-RC,Sullins,"1x6: VCC, GND, TX, RX, PPS, VBCKP",Connector_PinHeader_2.54mm:PinHeader_1x06_P2.54mm_Vertical,Navigation,0.65,0.65
51,1,U6,ICM-20948,ICM-20948,TDK InvenSense,"9-axis IMU, I2C",LoRa_Boat_Controller_V2:QFN-24_3x3mm_P0.4mm_NoEP,Navigation,11.50,11.50
52,2,R23 R24,2.2k,RC0603FR-072K2L,Yageo,I2C SCL pull-up,Resistor_SMD:R_0603_1608Metric,Navigation,0.10,0.20
53,1,J2,ESC,B3B-XH-A(LF)(SN),JST,"1: signal 5 V, 2: BEC in, 3: GND",Connector_JST:JST_XH_B3B-XH-A_1x03_P2.50mm_Vertical,Actuators,0.25,0.25
54,1,J3,SERVO,B3B-XH-A(LF)(SN),JST,"1: signal 5 V, 2: VSERVO out, 3: GND",Connector_JST:JST_XH_B3B-XH-A_1x03_P2.50mm_Vertical,Actuators,0.25,0.25
55,2,U4 U5,74AHCT1G125,SN74AHCT1G125DBVR,Texas Instruments,ESC PWM 3.3 -> 5 V buffer,Package_TO_SOT_SMD:SOT-23-5,Actuators,0.45,0.90
56,2,D10 D11,PESD5V0S1BA,"PESD5V0S1BA,115",Nexperia,ESC signal ESD,Diode_SMD:D_SOD-323,Actuators,0.25,0.50
57,1,J6,USB-C,USB4105-GF-A,GCT,USB 2.0 device console,Connector_USB:USB_C_Receptacle_GCT_USB4105-xx-A_16P_TopMnt_Horizontal,Debug,1.10,1.10
58,1,U7,USBLC6-2SC6,USBLC6-2SC6,STMicroelectronics,USB ESD,Package_TO_SOT_SMD:SOT-23-6,Debug,0.55,0.55
59,1,J7,SWD,FTSH-105-01-L-DV-K,Samtec,ARM 10-pin Cortex debug,Connector_PinHeader_1.27mm:PinHeader_2x05_P1.27mm_Vertical_SMD,Debug,3.20,3.20
60,1,TP1,ESC_PWM,,,MCU-side ESC PWM,TestPoint:TestPoint_Pad_D1.5mm,Actuators,,
61,1,TP2,SERVO_PWM,,,MCU-side servo PWM,TestPoint:TestPoint_Pad_D1.5mm,Actuators,,
62,1,TP3,+3V3,,,,TestPoint:TestPoint_Pad_D1.5mm,Power,,
63,1,TP4,VSERVO,,,,TestPoint:TestPoint_Pad_D1.5mm,Power,,
64,1,TP5,VIN_RAW,,,,TestPoint:TestPoint_Pad_D1.5mm,Power,,
65,1,TP6,GND,,,,TestPoint:TestPoint_Pad_D1.5mm,Power,,
66,1,TP7,PPS,,,,TestPoint:TestPoint_Pad_D1.5mm,Navigation,,
67,4,H1 H2 H3 H4,M3,,,Mounting hole,MountingHole:MountingHole_3.2mm_M3,Power,,
,118,"TOTAL (board only, qty 1, catalogue prices as of 2026-09-16)",,,,,,,,53.80

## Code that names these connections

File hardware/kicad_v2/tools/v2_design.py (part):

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    'Q1':  (('Transistor_FET', 'AO3401A'), 'Package_TO_SOT_SMD:SOT-23', 'AO3401A', 'AO3401A', 'Alpha & Omega', 'Power', 'P-MOSFET reverse-polarity protection (-30 V, 4 A)'),
    'D2':  (('Device', 'D_Zener'), 'Diode_SMD:D_SOD-123', '10V', 'BZT52C10-7-F', 'Diodes Inc', 'Power', 'Gate-source clamp for Q1 (10 V: AO3401A Vgs max is 12 V, review A-10)'),
    'R1':  (('Device', 'R'), 'Resistor_SMD:R_0603_1608Metric', '100k', 'RC0603FR-07100KL', 'Yageo', 'Power', 'Q1 gate pull-down'),
    'D1':  (('Diode', 'SMAJ33A'), 'Diode_SMD:D_SMA', 'SMAJ33A', 'SMAJ33A', 'Littelfuse', 'Power', '33 V unidirectional TVS on VIN_RAW (pin 1 = cathode to VIN_RAW)'),
    'C1':  (('Device', 'C_Polarized'), 'Capacitor_SMD:CP_Elec_6.3x7.7', '47uF 50V', 'EEE-FK1H470P', 'Panasonic', 'Power', 'Bulk input capacitor'),
    'C2':  (('Device', 'C'), 'Capacitor_SMD:C_1210_3225Metric', '10uF 50V', 'GRM32ER71H106KA12L', 'Murata', 'Power', 'Input ceramic'),
    'R33': (('Device', 'R'), 'Resistor_SMD:R_2512_6332Metric', '0.02R 1W', 'CRA2512-FZ-R020ELF', 'Bourns', 'Power', 'Board current shunt (REQ-PWR-06)'),
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
# STM32F446RET6 LQFP-64 pin numbers used below (DS10693 Table 10)
U1 = {'VBAT': 1, 'PC13': 2, 'PC14': 3, 'PC15': 4, 'PH0': 5, 'PH1': 6, 'NRST': 7, 'PC0': 8, 'PC1': 9, 'PC2': 10, 'PC3': 11, 'VSSA': 12, 'VDDA': 13,
      'PA0': 14, 'PA1': 15, 'PA2': 16, 'PA3': 17, 'VSS1': 18, 'VDD1': 19, 'PA4': 20, 'PB0': 26, 'VCAP': 30, 'VSS2': 31, 'VDD2': 32, 'PC6': 37,
      'PA8': 41, 'PA9': 42, 'PA11': 44, 'PA12': 45, 'PA13': 46, 'VSS3': 47, 'VDD3': 48, 'PA14': 49, 'PC10': 51, 'PC11': 52, 'PB3': 55,
      'PB5': 57, 'PB6': 58, 'PB7': 59, 'BOOT0': 60, 'VSS4': 63, 'VDD4': 64}
def u1(name): return f'U1-{U1[name]}'

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    'PGATE': ['Q1-1', 'R1-1', 'D2-2'],
    'VIN_RAW': ['Q1-2', 'D2-1', 'D1-1', 'C1-1', 'C2-1', 'R33-1', 'U8-3', 'R31-1', 'TP5-1'],
    'VIN_BUCK': ['R33-2', 'U8-4', 'U2-2', 'R2-1', 'U3-3', 'R6-1', 'C10-1'],
    'ISENSE': ['U8-1', 'C37-1', u1('PA4')],
    'VBAT_SENSE': ['R31-2', 'R32-1', 'C36-1', u1('PA2')],
    'EN_3V3': ['U2-1', 'R2-2'],
    'SW_3V3': ['U2-3', 'L1-1', 'D3-2', 'C3-1'],
    'BST_3V3': ['U2-4', 'R3-2'],
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    'VCAP1': [u1('VCAP'), 'C20-1'],
    'NRST': [u1('NRST'), 'C24-1', 'SW1-1', 'J7-10'],
    'BOOT0': [u1('BOOT0'), 'R16-1'],
    'HSE_IN': [u1('PH0'), 'Y1-1', 'C25-1'],
    'HSE_OUT': [u1('PH1'), 'Y1-3', 'C26-1'],
    'LSE_IN': [u1('PC14'), 'Y2-1', 'C27-1'],
    'LSE_OUT': [u1('PC15'), 'Y2-2', 'C28-1'],
    'LED_PWR': ['R29-2', 'D5-2'],
    'LED_LINK': [u1('PC1'), 'R30-1'], 'LED_LINK_A': ['R30-2', 'D6-2'],
    'LED_FIX': [u1('PC2'), 'R34-1'], 'LED_FIX_A': ['R34-2', 'D7-2'],
    'LED_FAULT': [u1('PC3'), 'R35-1'], 'LED_FAULT_A': ['R35-2', 'D8-2'],
    'LORA_FILT': ['FB2-2', 'FB3-1', 'C29-1'],
    'LORA_VCC': ['FB3-2', 'C30-1', 'C31-1', 'C32-1', 'J4-1'],
    'LORA_TX_PA0': [u1('PA0'), 'R17-1'], 'LORA_RXD': ['R17-2', 'J4-3'],
    'LORA_RX_PA1': [u1('PA1'), 'R18-1'], 'LORA_TXD': ['R18-2', 'J4-4'],
    'LORA_NRST_PA3': [u1('PA3'), 'R19-1'], 'LORA_NRST': ['R19-2', 'J4-2'],
    'GNSS_TX_PC10': [u1('PC10'), 'R20-1'], 'GNSS_RXD': ['R20-2', 'J5-4'],
    'GNSS_RX_PC11': [u1('PC11'), 'R21-1'], 'GNSS_TXD': ['R21-2', 'J5-3'],
    'PPS_PB0': [u1('PB0'), 'R22-1', 'TP7-1'], 'GNSS_PPS': ['R22-2', 'J5-5'],
    'I2C1_SCL': [u1('PB6'), 'R23-2', 'U6.SCL/SCLK'],
    'I2C1_SDA': [u1('PB7'), 'R24-2', 'U6.SDA/SDI'],
    'IMU_INT': [u1('PB5'), 'U6.INT1'],
    'IMU_REGOUT': ['U6.REGOUT', 'C33-1'],
    'PWM_ESC_PC6': [u1('PC6'), 'U4-2', 'R14-1', 'TP1-1'],
    'ESC_SIG_5V': ['U4-4', 'R10-1'], 'ESC_SIG': ['R10-2', 'R11-1', 'D10-1', 'J2-1'],
    'PWM_SERVO_PA8': [u1('PA8'), 'U5-2', 'R15-1', 'TP2-1'],
    'SERVO_SIG_5V': ['U5-4', 'R12-1'], 'SERVO_SIG': ['R12-2', 'R13-1', 'D11-1', 'J3-1'],
    'VBUS': ['J6-A4', 'J6-A9', 'J6-B4', 'J6-B9', 'U7-5', 'R27-1'],
    'VBUS_SENSE': ['R27-2', 'R28-1', u1('PA9')],
    'USB_CC1': ['J6-A5', 'R25-1'], 'USB_CC2': ['J6-B5', 'R26-1'],
    'USB_DP_CONN': ['J6-A6', 'J6-B6', 'U7-1'], 'USB_DM_CONN': ['J6-A7', 'J6-B7', 'U7-3'],
    'USB_DP': ['U7-6', u1('PA12')], 'USB_DM': ['U7-4', u1('PA11')],
    'SWDIO': [u1('PA13'), 'J7-2'], 'SWCLK': [u1('PA14'), 'J7-4'], 'SWO': [u1('PB3'), 'J7-6'],
}
POWER_NETS = {'GND': ('power', 'GND', 'down'), '+3V3': ('power', '+3V3', 'up'), 'VIN_RAW': ('LoRa_Boat_Controller', 'VIN_RAW', 'up'),
              'VSERVO': (PROJ, 'VSERVO', 'up'), 'VBUS': ('power', 'VBUS', 'up')}
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    ('Power', 'Power.kicad_sch', 'A3', 'REQ-PWR-01..08: XT30 input, fuse, reverse P-FET, TVS, current shunt, 3.3 V buck (V1 circuit corrected), 5 V servo buck + BEC OR-ing, battery ADC divider'),
    ('MCU', 'MCU.kicad_sch', 'A3', 'REQ-MCU-01..05, REQ-DBG-02: STM32F446RET6, VCAP to VSS, VDDA filter, HSE 8 MHz + LSE, NRST/BOOT0, LEDs'),
    ('Radio', 'Radio.kicad_sch', 'A4', 'REQ-RF-01/04/05: RYLR998(_M4) socket, pi filter to GND, series resistors, NRST from MCU; antenna via SMA bulkhead pigtail'),
    ('Navigation', 'Navigation.kicad_sch', 'A4', 'REQ-NAV-01/02/05: GNSS 1x6 with PPS -> PB0 (TIM3_CH3), ICM-20948 on I2C1'),
    ('Actuators', 'Actuators.kicad_sch', 'A4', 'REQ-CTL-03/05, REQ-PWR-03: 74AHCT1G125 5 V buffers with input pull-downs, series R + TVS, ESC/SERVO JST XH; VSERVO never +3V3'),
    ('Debug', 'Debug.kicad_sch', 'A4', 'REQ-DBG-01: USB-C console with USBLC6 ESD and CC pull-downs; ARM 10-pin SWD'),
]
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
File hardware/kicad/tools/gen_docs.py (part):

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    'BST': ('U6 BST to R3 (51 R)', 'unchanged'), 'BST_RC': ('between R3 and C12 (0.1 uF) - the bootstrap RC per Nisshinbo DS', 'unchanged'),
    'EN': ('U6 CE via R4 5.1 k from VIN_RAW (CE has no internal pull)', 'V2: MCU-controlled enable optional'),
    'FB_DIV': ('U6 VFB with R1 15 k / R2 4.7 k / C14 470 pF -> Vout = 0.8*(1+15/4.7) = 3.35 V', 'unchanged'),
    'ADC_VBAT': ('R5 30 k / R6 10 k divider to PA2 (ADC1_IN2); firmware never enables the ADC', 'V2: read it; add filter cap'),
    'VCAP1': ('U3 pin 30 VCAP_1 to CEXT-1; CEXT-2 returns to +3V3 instead of VSS (V1 defect)', 'V2: 4.7 uF to VSS'),
    'LORA_VCC': ('LoRa header VDD after ferrite L3, with C21 10 uF, C22 0.1 uF, C23 (22 or 47 pF) to GND', 'V2: same filter, verify TX current'),
    'LORA_FILT': ('between L4 (from +3V3) and L3; C20 10 uF to +3V3 (not GND!)', 'V2: cap to GND'),
    'LORA_TX_PA0': ('UART4_TX -> LoRa RXD', 'series resistor in V2'), 'LORA_RX_PA1': ('LoRa TXD -> UART4_RX', 'series resistor in V2'),
    'LORA_RST_PA3': ('PA3 -> LoRa NRST; firmware never drives it', 'V2 firmware drives reset'),
    'GPS_PB0': ('PB0 GPIO output (held LOW by firmware) -> GPS header pin 3', 'V2: PPS input instead'),
    'GPS_RX_PC11': ('GPS TXD -> USART3_RX', 'unchanged'), 'GPS_TX_PC10': ('USART3_TX -> GPS RXD (also carries debug prints)', 'V2: separate console'),
    'CAN_STB_PA11': ('PA11 (= CAN1_RX pin!) drives U5 STB', 'V2: STB on a plain GPIO or tied low'),
    'CAN_RXD_PA10': ('U5 RXD -> PA10, which has no CAN alternate function', 'V2: RXD to PA11'),
    'CAN_TXD_PA12': ('PA12 CAN1_TX -> U5 TXD (correct)', 'unchanged'),
    'CANH': ('U5 pin 7 (CANH) -> CANHEADER pin 3', 'V2: termination option'), 'CANL': ('U5 pin 6 (CANL) -> CANHEADER pin 4', 'V2: termination option'),
    'CAN_VCC': ('U5 VCC (needs 4.5-5.5 V) supplied from CANHEADER-2, C1 0.1 uF', 'V2: on-board 5 V'),
    'PWM_PA8_ESCHDR': ('PA8/TIM1_CH1 -> SPEEDCONTROLLER-2 (and TP1); firmware calls PA8 "rudder"', 'V2: named by function, series R + ESD'),
    'PWM_PC6_SERVOHDR': ('PC6/TIM3_CH1 -> STEERINGSERVO-2 (and TP3); firmware calls PC6 "motor"', 'V2: named by function, series R + ESD'),
    'SWDIO': ('PA13 -> JTAG-2', 'unchanged'), 'SWCLK': ('PA14 -> JTAG-4', 'unchanged'), 'SWO_TDO': ('PB3 -> JTAG-6', 'unchanged'),
    'TDI': ('PA15 -> JTAG-8', 'V2: SWD only, free PA15/PB3'), 'NRST': ('U3 NRST -> JTAG-10; no external RC', 'V2: 100 nF on NRST'),
    'VBAT': ('U3 pin 1 only - floating on V1', 'V2: tie to VDD'),
}

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    nc = [f'U3-{p}' for p in ['2','3','4','5','6','8','9','10','11','20','21','22','23','24','25','27','28','29','33','34','35','36','38','39','40','42','53','54','56','57','58','59','60','61','62']] + ['U5-5', 'JTAG1-7']
    lines += ['', '## Unconnected pins (NC in pstxnet.dat)', '', 'U3: ' + ', '.join(p for p in nc if p.startswith('U3')) + ' (35 MCU pins incl. BOOT0 pin 60 and the HSE/LSE pins 3, 4, 5, 6); U5-5 (NC on the H variant); JTAG1-7 (key).', '',
              '## Reading the names', '',
              '- Signal nets are named by MCU pin so the PWM swap question cannot recur: `PWM_PA8_ESCHDR` reaches the header the silkscreen calls SPEEDCONTROLLER, `PWM_PC6_SERVOHDR` the STEERINGSERVO header.',
              '- `CANL`/`CANH` follow the TCAN1042H pin functions (pin 6 = CANL, pin 7 = CANH); the March 2026 NETLIST.md had them reversed.',
              '- Power symbols in the schematic: `GND`, `+3V3`, `VIN_RAW`.']
    open(os.path.join(DOCS, 'NETLIST.md'), 'w', encoding='utf-8', newline='\n').write('\n'.join(lines) + '\n')

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    rows += ['', '## Images (docs/img)', '', '| Image | Purpose |', '|---|---|']
    IMGW = {
        'v1_pcb_top.png': 'KiCad raytraced render of the reconstructed V1 board, top', 'v1_pcb_bottom.png': 'KiCad raytraced render, bottom',
        'v1_schematic.pdf': 'All V1 schematic sheets (PDF)', 'v1_evidence_pwm.png': 'Copper evidence: PA8 -> SPEEDCONTROLLER, PC6 -> STEERINGSERVO',
        'v1_evidence_vcap.png': 'Copper evidence: CEXT between VCAP_1 (pin 30) and +3V3', 'v1_evidence_can.png': 'Copper evidence: PA12 -> TXD, PA11 -> STB, PA10 -> RXD',
        'v2_pcb_top.png': 'KiCad raytraced render of the V2 board (autorouted draft), top', 'v2_pcb_bottom.png': 'KiCad raytraced render of the V2 board, bottom',
        'v2_schematic.pdf': 'All V2 schematic sheets (PDF)',
    }
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
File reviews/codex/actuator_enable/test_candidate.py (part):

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            self.validate()

    def test_input_channels_crossed_rejected(self):
        move_pin(self.candidate, "U4", "4", "/PWM_ESC_PC6")
        move_pin(self.candidate, "U4", "5", "/PWM_SERVO_PA8")
        with self.rejected("exact ACT-02 contract"):
            self.validate()

    def test_output_channels_crossed_rejected(self):
        move_pin(self.candidate, "U4", "1", "/Actuators/ESC_SIG_5V")
        move_pin(self.candidate, "U4", "8", "/Actuators/SERVO_SIG_5V")
        with self.rejected("exact ACT-02 contract"):
            self.validate()

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            self.validate()

    def test_output_supply_on_vservo_rejected(self):
        move_pin(self.candidate, "U4", "7", "VSERVO")
        with self.rejected("exact ACT-02 contract"):
            self.validate()

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
    def test_diode_polarity_changed_rejected(self):
        move_pin(self.candidate, "D4", "1", "/Power/+5V_BUCK")
        move_pin(self.candidate, "D4", "2", "VSERVO")
        with self.rejected("Outside-boundary pin memberships"):
            self.validate()

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
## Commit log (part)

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2026-04-01 Initial Upload
